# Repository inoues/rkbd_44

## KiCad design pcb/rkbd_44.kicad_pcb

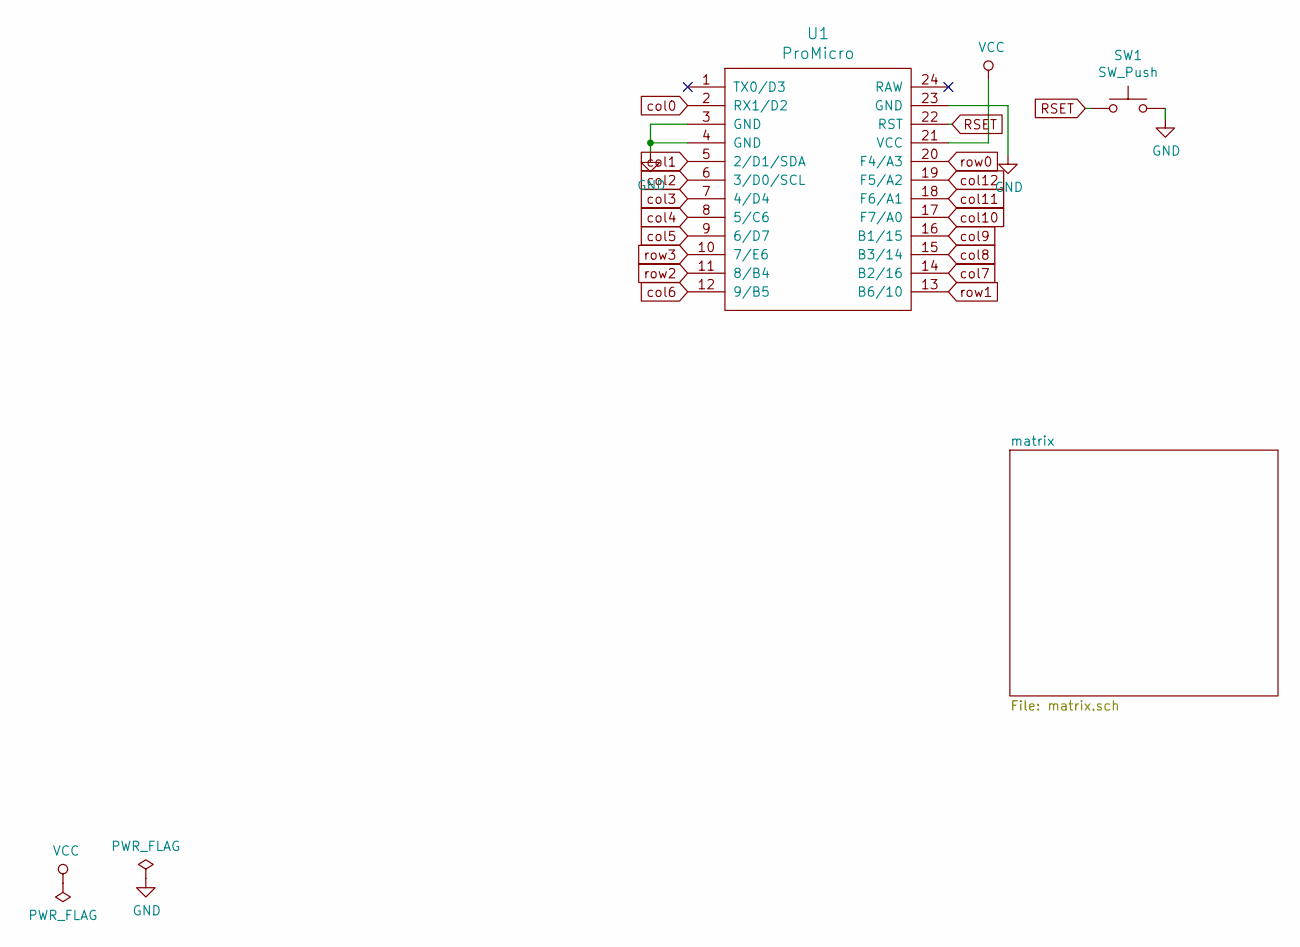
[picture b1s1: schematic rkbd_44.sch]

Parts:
SW1: SW_Push; SKQG-1155865
U1: ProMicro; ProMicro_v3.5

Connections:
GND: SW1.2, U1.3 (GND), U1.4 (GND), U1.23 (GND)
RSET: SW1.1, U1.22 (RST)
VCC: U1.21 (VCC)
col0: U1.2 (RX1/D2); also elsewhere on the board
col1: U1.5 (2/D1/SDA); also elsewhere on the board
col2: U1.6 (3/D0/SCL); also elsewhere on the board
col3: U1.7 (4/D4); also elsewhere on the board
col4: U1.8 (5/C6); also elsewhere on the board
col5: U1.9 (6/D7); also elsewhere on the board
col6: U1.12 (9/B5); also elsewhere on the board
col7: U1.14 (B2/16); also elsewhere on the board
col8: U1.15 (B3/14); also elsewhere on the board
col9: U1.16 (B1/15); also elsewhere on the board
col10: U1.17 (F7/A0); also elsewhere on the board
col11: U1.18 (F6/A1); also elsewhere on the board
col12: U1.19 (F5/A2); also elsewhere on the board
row0: U1.20 (F4/A3); also elsewhere on the board
row1: U1.13 (B6/10); also elsewhere on the board
row2: U1.11 (8/B4); also elsewhere on the board
row3: U1.10 (7/E6); also elsewhere on the board

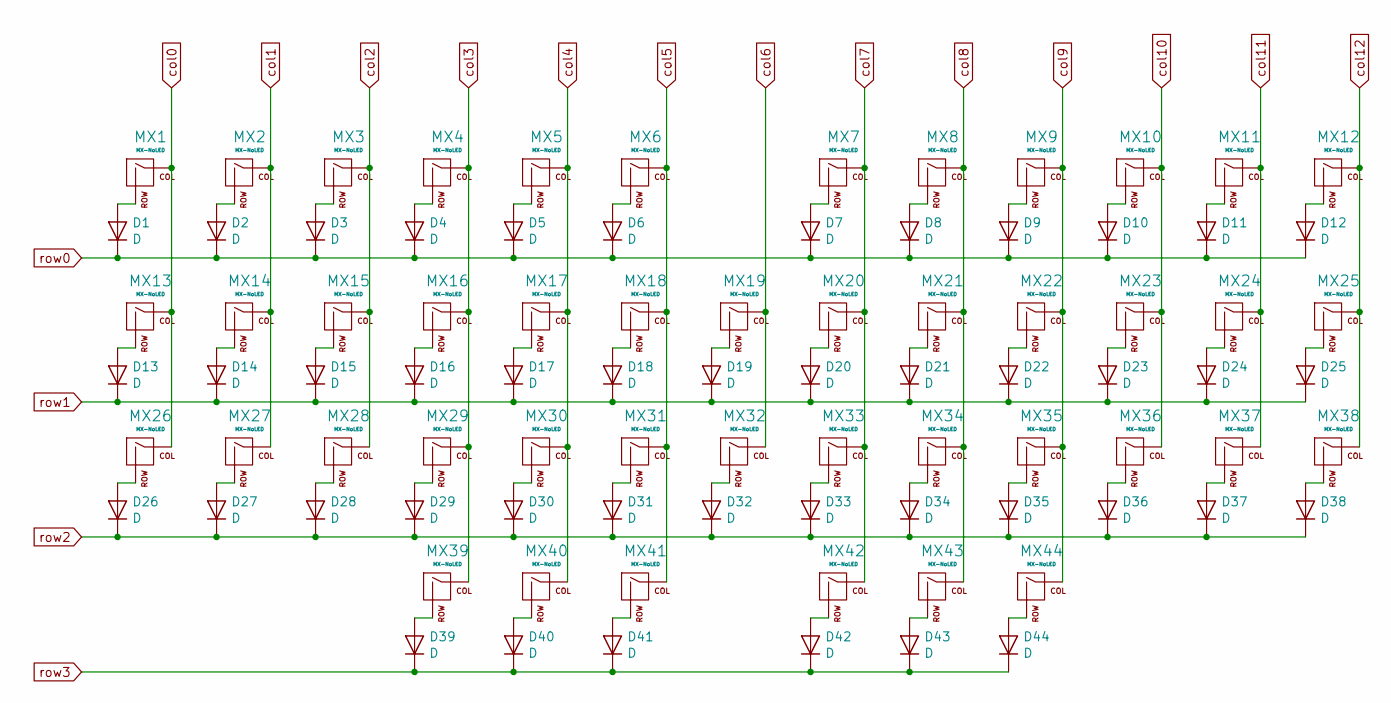
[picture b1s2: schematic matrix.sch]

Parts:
D1, D2, D3, D4, D5, D6, D7, D8, D9, D10, D11, D12, D13, D14, D15, D16, D17, D18, D19, D20, D21, D22, D23, D24, D25, D26, D27, D28, D29, D30, D31, D32, D33, D34, D35, D36, D37, D38, D39, D40, D41, D42, D43, D44: D; D_SOD-123
MX1, MX2, MX3, MX4, MX5, MX6, MX7, MX8, MX9, MX10, MX11, MX12, MX13, MX14, MX15, MX16, MX17, MX18, MX19, MX20, MX21, MX22, MX23, MX24, MX25, MX26, MX27, MX28, MX29, MX30, MX31, MX32, MX33, MX34, MX35, MX36, MX37, MX38, MX39, MX40, MX43, MX44: MX-NoLED; MXOnly-1U-NoLED
MX41, MX42: MX-NoLED; MXOnly-1.25U-NoLED

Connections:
unnamed: D1.2 (A), MX1.2 (ROW)
unnamed: D2.2 (A), MX2.2 (ROW)
unnamed: D3.2 (A), MX3.2 (ROW)
unnamed: D4.2 (A), MX4.2 (ROW)
unnamed: D5.2 (A), MX5.2 (ROW)
unnamed: D6.2 (A), MX6.2 (ROW)
unnamed: D7.2 (A), MX7.2 (ROW)
unnamed: D8.2 (A), MX8.2 (ROW)
unnamed: D9.2 (A), MX9.2 (ROW)
unnamed: D10.2 (A), MX10.2 (ROW)
unnamed: D11.2 (A), MX11.2 (ROW)
unnamed: D12.2 (A), MX12.2 (ROW)
unnamed: D13.2 (A), MX13.2 (ROW)
unnamed: D14.2 (A), MX14.2 (ROW)
unnamed: D15.2 (A), MX15.2 (ROW)
unnamed: D16.2 (A), MX16.2 (ROW)
unnamed: D17.2 (A), MX17.2 (ROW)
unnamed: D18.2 (A), MX18.2 (ROW)
unnamed: D19.2 (A), MX19.2 (ROW)
unnamed: D20.2 (A), MX20.2 (ROW)
unnamed: D21.2 (A), MX21.2 (ROW)
unnamed: D22.2 (A), MX22.2 (ROW)
unnamed: D23.2 (A), MX23.2 (ROW)
unnamed: D24.2 (A), MX24.2 (ROW)
unnamed: D25.2 (A), MX25.2 (ROW)
unnamed: D26.2 (A), MX26.2 (ROW)
unnamed: D27.2 (A), MX27.2 (ROW)
unnamed: D28.2 (A), MX28.2 (ROW)
unnamed: D29.2 (A), MX29.2 (ROW)
unnamed: D30.2 (A), MX30.2 (ROW)
unnamed: D31.2 (A), MX31.2 (ROW)
unnamed: D32.2 (A), MX32.2 (ROW)
unnamed: D33.2 (A), MX33.2 (ROW)
unnamed: D34.2 (A), MX34.2 (ROW)
unnamed: D35.2 (A), MX35.2 (ROW)
unnamed: D36.2 (A), MX36.2 (ROW)
unnamed: D37.2 (A), MX37.2 (ROW)
unnamed: D38.2 (A), MX38.2 (ROW)
unnamed: D39.2 (A), MX39.2 (ROW)
unnamed: D40.2 (A), MX40.2 (ROW)
unnamed: D41.2 (A), MX41.2 (ROW)
unnamed: D42.2 (A), MX42.2 (ROW)
unnamed: D43.2 (A), MX43.2 (ROW)
unnamed: D44.2 (A), MX44.2 (ROW)
col0: MX1.1 (COL), MX13.1 (COL), MX26.1 (COL); also elsewhere on the board
col1: MX2.1 (COL), MX14.1 (COL), MX27.1 (COL); also elsewhere on the board
col2: MX3.1 (COL), MX15.1 (COL), MX28.1 (COL); also elsewhere on the board
col3: MX4.1 (COL), MX16.1 (COL), MX29.1 (COL), MX39.1 (COL); also elsewhere on the board
col4: MX5.1 (COL), MX17.1 (COL), MX30.1 (COL), MX40.1 (COL); also elsewhere on the board
col5: MX6.1 (COL), MX18.1 (COL), MX31.1 (COL), MX41.1 (COL); also elsewhere on the board
col6: MX19.1 (COL), MX32.1 (COL); also elsewhere on the board
col7: MX7.1 (COL), MX20.1 (COL), MX33.1 (COL), MX42.1 (COL); also elsewhere on the board
col8: MX8.1 (COL), MX21.1 (COL), MX34.1 (COL), MX43.1 (COL); also elsewhere on the board
col9: MX9.1 (COL), MX22.1 (COL), MX35.1 (COL), MX44.1 (COL); also elsewhere on the board
col10: MX10.1 (COL), MX23.1 (COL), MX36.1 (COL); also elsewhere on the board
col11: MX11.1 (COL), MX24.1 (COL), MX37.1 (COL); also elsewhere on the board
col12: MX12.1 (COL), MX25.1 (COL), MX38.1 (COL); also elsewhere on the board
row0: D1.1 (K), D2.1 (K), D3.1 (K), D4.1 (K), D5.1 (K), D6.1 (K), D7.1 (K), D8.1 (K), D9.1 (K), D10.1 (K), D11.1 (K), D12.1 (K); also elsewhere on the board
row1: D13.1 (K), D14.1 (K), D15.1 (K), D16.1 (K), D17.1 (K), D18.1 (K), D19.1 (K), D20.1 (K), D21.1 (K), D22.1 (K), D23.1 (K), D24.1 (K), D25.1 (K); also elsewhere on the board
row2: D26.1 (K), D27.1 (K), D28.1 (K), D29.1 (K), D30.1 (K), D31.1 (K), D32.1 (K), D33.1 (K), D34.1 (K), D35.1 (K), D36.1 (K), D37.1 (K), D38.1 (K); also elsewhere on the board
row3: D39.1 (K), D40.1 (K), D41.1 (K), D42.1 (K), D43.1 (K), D44.1 (K); also elsewhere on the board

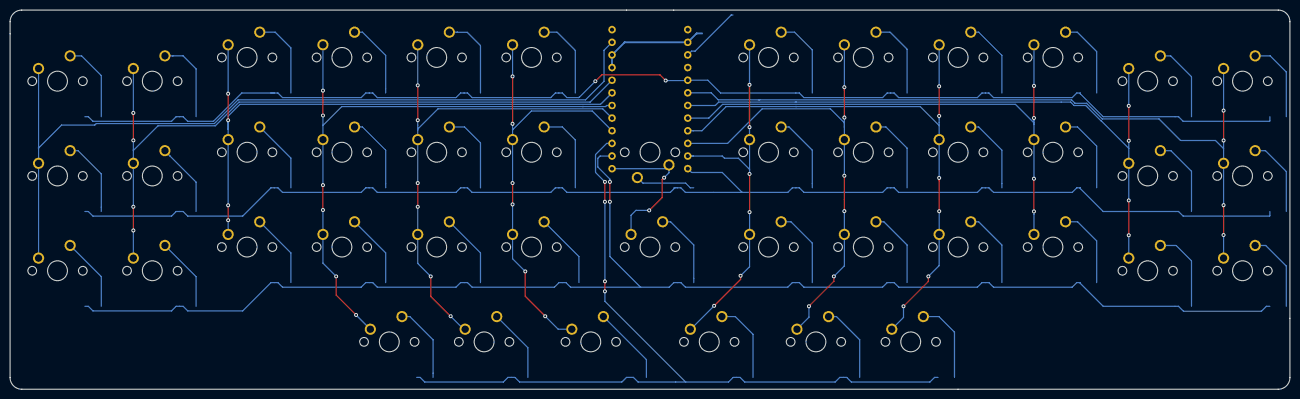
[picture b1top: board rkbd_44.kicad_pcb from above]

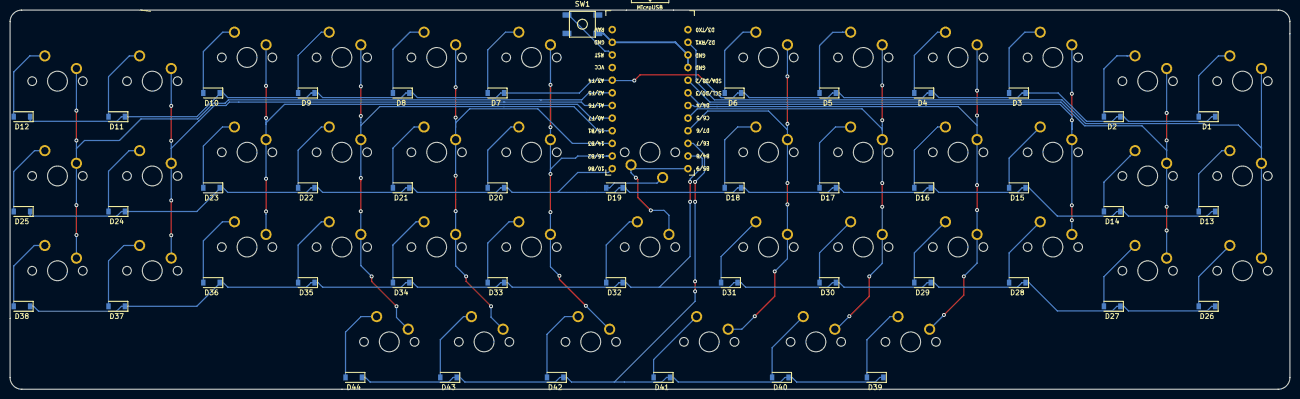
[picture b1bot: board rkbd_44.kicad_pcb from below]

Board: 2 copper layers, 257.2 x 76.2 mm, 90 parts (46 on the bottom side), 63 nets.

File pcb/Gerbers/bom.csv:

"ID";"参照記号";"パッケージ";"数";"名称";"Supplier and ref";
1;"MX7,MX19,MX44,MX43,MX40,MX39,MX38,MX37,MX36,MX35,MX34,MX33,MX32,MX31,MX30,MX29,MX28,MX27,MX26,MX25,MX24,MX23,MX22,MX21,MX20,MX18,MX17,MX16,MX15,MX14,MX13,MX12,MX11,MX10,MX9,MX8,MX6,MX5,MX4,MX3,MX2,MX1";"MXOnly-1U-NoLED";42;"MX-NoLED";;;
2;"U1";"ProMicro_v3.5";1;"ProMicro";;;
3;"SW1";"SKQG-1155865";1;"SW_Push";;;
4;"MX42,MX41";"MXOnly-1.25U-NoLED";2;"MX-NoLED";;;
5;"D44,D43,D42,D41,D40,D39,D38,D37,D36,D35,D34,D33,D32,D31,D30,D29,D28,D27,D26,D25,D24,D23,D22,D21,D20,D19,D18,D17,D16,D15,D14,D13,D12,D11,D10,D9,D8,D7,D6,D5,D4,D3,D2,D1";"D_SOD-123";44;"D";;;

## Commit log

2020-01-25 init kicad project
2020-01-25 add submodules
2020-01-25 add submodule at pcb dir
2020-01-25 set symbole lib, footprint lib
2020-01-25 create schematic
2020-01-25 pcb new
2020-01-29 footprint layout
2020-01-30 change mcu position, change sw footprint
2020-02-02 add cutting line
2020-02-03 Routing all, Ground fills
2020-02-03 fix mcu routing
2020-02-05 Fill zones, fix drc erro
2020-02-21 mcu change promicro
2020-02-21 export gerber files
